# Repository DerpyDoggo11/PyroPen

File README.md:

# Pyropen
A pen with an embedded charlieplexed screen and thermal sensor

## 3D Model Preview

## 3D PCB Preview

## Wiring

## Schematic

## Introduction
Hobby electronics projects can come with a lot of dangers, especially if there is a short between ground and the main voltage line (3.3v) through a component, which is one of the most common faults when hand soldering. These components can get really hot which means placing your finger to sense the temperature is not a super safe option, and is also not very possible for really small components in tight areas. Theres also hundreds of other applications like seeing if a soldering iron is at the good temperature or if something is being heated properly where touching it is not very recommended... 

My solution to this is the PyroPen - a portable thermal sensor that fits in the palm of your hand! It can also replace a regular pen, meaning that you have this sensor on you wherever you go. 

## Bill of Materials 

### 5 Pens:

| Quantity | Components | Price | Link |
|--------- |----------|----------| -----|
| 5  | D1 Mini Pen Refill  (around 67mm long) | $6 | [here](https://www.aliexpress.us/item/3256810502408645.html?spm=a2g0o.productlist.main.1.6d809qLy9qLyLj&algo_pvid=76f2cf68-db1d-471b-9ad9-c0e175543bda&algo_exp_id=76f2cf68-db1d-471b-9ad9-c0e175543bda-0&pdp_ext_f=%7B%22order%22%3A%22431%22%2C%22eval%22%3A%221%22%2C%22fromPage%22%3A%22search%22%7D&pdp_npi=6%40dis%21USD%218.80%216.16%21%21%2158.72%2141.10%21%402101e80b17891628832691912e0dab%2112000053197611078%21sea%21US%217493938711%21X%211%210%21n_tag%3A-29919%3Bd%3Ad260408f%3Bm03_new_user%3A-29895&curPageLogUid=INQ9floTcDND&utparam-url=scene%3Asearch%7Cquery_from%3A%7Cx_object_id%3A1005010688723397%7C_p_origin_prod%3A)
| 1 | Plexiglass sheet | $5 | [here](https://www.aliexpress.us/item/3256807722386926.html?spm=a2g0o.productlist.main.2.39f129e2SERr2S&algo_pvid=185f7068-e484-4aa3-9ff3-0e65a2acbd56&algo_exp_id=185f7068-e484-4aa3-9ff3-0e65a2acbd56-1&pdp_ext_f=%7B%22order%22%3A%22156%22%2C%22eval%22%3A%221%22%2C%22fromPage%22%3A%22search%22%7D&pdp_npi=6%40dis%21USD%218.44%215.23%21%21%2156.35%2134.94%21%402101c4ea17891631287926600e102c%2112000042797704390%21sea%21US%217493938711%21X%211%210%21n_tag%3A-29919%3Bd%3Ad260408f%3Bm03_new_user%3A-29895&curPageLogUid=IFVzF4QWo7zW&utparam-url=scene%3Asearch%7Cquery_from%3A%7Cx_object_id%3A1005007908701678%7C_p_origin_prod%3A)
| 1 | M10 tap and M10 die | $10-25 | [here](https://www.aliexpress.us/item/3256806490105856.html?spm=a2g0o.productlist.main.1.787f45362GMN3x&algo_pvid=6b4764b8-9f9b-4b4b-abaf-7ee7ff8e24d2&algo_exp_id=6b4764b8-9f9b-4b4b-abaf-7ee7ff8e24d2-0&pdp_ext_f=%7B%22order%22%3A%222091%22%2C%22eval%22%3A%221%22%2C%22fromPage%22%3A%22search%22%7D&pdp_npi=6%40dis%21USD%2191.27%2124.16%21%21%2191.27%2124.16%21%402101d9ef17891629153167158e0d3e%2112000037989416687%21sea%21US%217493938711%21X%211%210%21n_tag%3A-29919%3Bd%3Ad260408f%3Bm03_new_user%3A-29895%3BpisId%3A5000000216826354&curPageLogUid=6mPafcKNUYwu&utparam-url=scene%3Asearch%7Cquery_from%3A%7Cx_object_id%3A1005006676420608%7C_p_origin_prod%3A#nav-specification)
| 1 | Black Silicone Sheet | $6 | [here](https://www.aliexpress.us/item/3256803477740534.html?spm=a2g0o.productlist.main.2.18d8BtN8BtN8hz&algo_pvid=ee0522a2-58d0-4bcf-9e30-e4f22c28cf2e&algo_exp_id=ee0522a2-58d0-4bcf-9e30-e4f22c28cf2e-1&pdp_ext_f=%7B%22order%22%3A%22401%22%2C%22eval%22%3A%221%22%2C%22fromPage%22%3A%22search%22%7D&pdp_npi=6%40dis%21USD%216.57%216.57%21%21%216.57%216.57%21%402103081117891632978163784e1014%2112000026705712515%21sea%21US%217493938711%21X%211%210%21n_tag%3A-29919%3Bd%3Ad260408f%3Bm03_new_user%3A-29895&curPageLogUid=KVIebw9Xz1w2&utparam-url=scene%3Asearch%7Cquery_from%3A%7Cx_object_id%3A1005003664055286%7C_p_origin_prod%3A)
| 10 | Contact Springs | $3 | [here](https://www.aliexpress.us/item/3256811981198202.html?spm=a2g0o.productlist.main.22.77f10hiQ0hiQK3&algo_pvid=e18af909-f335-4400-8902-d4f17e02d908&algo_exp_id=e18af909-f335-4400-8902-d4f17e02d908-21&pdp_ext_f=%7B%22order%22%3A%22104%22%2C%22eval%22%3A%221%22%2C%22fromPage%22%3A%22search%22%7D&pdp_npi=6%40dis%21USD%212.11%212.11%21%21%2114.07%2114.07%21%402103094f17891662172853954e0ecd%2112000057659623320%21sea%21US%217493938711%21X%211%210%21n_tag%3A-29919%3Bd%3Ad260408f%3Bm03_new_user%3A-29895&curPageLogUid=K0owjtkuBRbz&utparam-url=scene%3Asearch%7Cquery_from%3A%7Cx_object_id%3A1005012167512954%7C_p_origin_prod%3A) 
| 5 | 5mm Piezoelectric Buzzers | $1 | [here](https://www.lcsc.com/product-detail/C76871.html?s_z=n_q_l_piezoelectric%2520ceramic%2520diaphragm&spm=wm.fly.bg.0.xh___wm.ssy.ml.0-0.ent&lcsc_vid=RwNdUQVeTwANA11XFlZZX1IHRwBZVVwDRlkNV1BWQQMxVlNeTlBYVFxWRldYUTsOAxUeFF5JWBYZEEoKFBINSQcJGk4%3D) 
| 5 | MLX Infrared Sensors | $44 | [here](https://www.lcsc.com/product-detail/C3663116.html?s_z=n_q_MLX90614%2520&spm=wm.fly.bg.0.xh&lcsc_vid=RwNdUQVeTwANA11XFlZZX1IHRwBZVVwDRlkNV1BWQQMxVlNeTlBYX1NQTlVfVjsOAxUeFF5JWBYZEEoKFBINSQcJGk4NBhADEA4cHktTRk8GEwkK)
| 5 | AAAA Batteries | $7 | [here](https://www.amazon.com/AmazonBasics-Everyday-Alkaline-Batteries-8-Pack/dp/B00LH3DTYS?crid=3SYUEZ4T84FRV&dib=eyJ2IjoiMSJ9.xJZDnwcXb6EhPXm3mujCAttCgFNsW5aKTzGClFgmbNEjNBc2EIEIb0whSA5f3VcD3A-52y31u_q1Zwa2tIzaYB4oMPsB5-F0LAKjcA06an0JA-MCbnHJLxW74Hy52UELYeB8vnAcLA--8-hO090HfCUW1_Jm4RTs1KzpswVWjnrPVgvfUBrpNFrdIDRPyOvtuVmp1lYjwbZ0h8qXp7lpeklCB14scTmb_KNGeEhvzpb2sc9qDL89ZA_GC0lTx49BjnFbOIMi3paBV0zKl9BSVV2KHnai9rwA-lfpRBzrJMg.HBTIVsixOTtFYGvLlxr646ElXtiAA0v_4nQW3vVoWGo&dib_tag=se&keywords=aaaa%2Bbatteries%2B10%2Bpack&qid=1789191829&rdc=1&sprefix=aaaa%2Bbatteries%2B10%2Bpac%2Caps%2C321&sr=8-9&th=1)
| 5 | Warm Leds | $1 | [here](https://www.lcsc.com/product-detail/C5440675.html?s_z=n_q_t_warm%2520white%2520led&spm=wm.fly.bg.10.stp___wm.ssy.tc.1.tz&lcsc_vid=RgRbBFdUEQJXXwUER1JXVV1QRQIPUgdUQgRYVAFRR1gxVlNeTlNdUVRWR1NcUzsOAxUeFF5JWBYZEEoKFBINSQcJGk4%3D) 
| 5 | PCBA for PyroPen | $60 | Uploaded PCB fabrication files to JLCPCB and assemble it.   
 
Total cost: **$157**

Cost per pen: **$31.4**

----

## Tools / Other parts:
- M10 Tap and Die (from BOM)
- Hot glue + hot glue gun (or super glue)
- Dremel
- Raspbbery Pi, or any other device that can be used to flash firmware to the ATTINY chip.
- 3D printer

## Assembly
1. 3D print the case and assembly 
2. Use the M10 Tap and Die to thread the three pieces at their corresponding places
3. Cut plexiglass and glue onto the screen case
4. Remove the tabs from the PCB with a dremel (required for meeting the PCBA size requirements)
5. Flash firmware to the PCB with a raspbbery pi (or other method)
6. Solder on the buzzer, MLX sensor, and contact springs to the PCB
7. Insert the assembly into the case.
8. Glue the PCB to the inside of the case with the screen facing out and the button in place
9. Insert the pen refill tightly into the case
10. Mount the remaining components into the case, insert battery, and seal

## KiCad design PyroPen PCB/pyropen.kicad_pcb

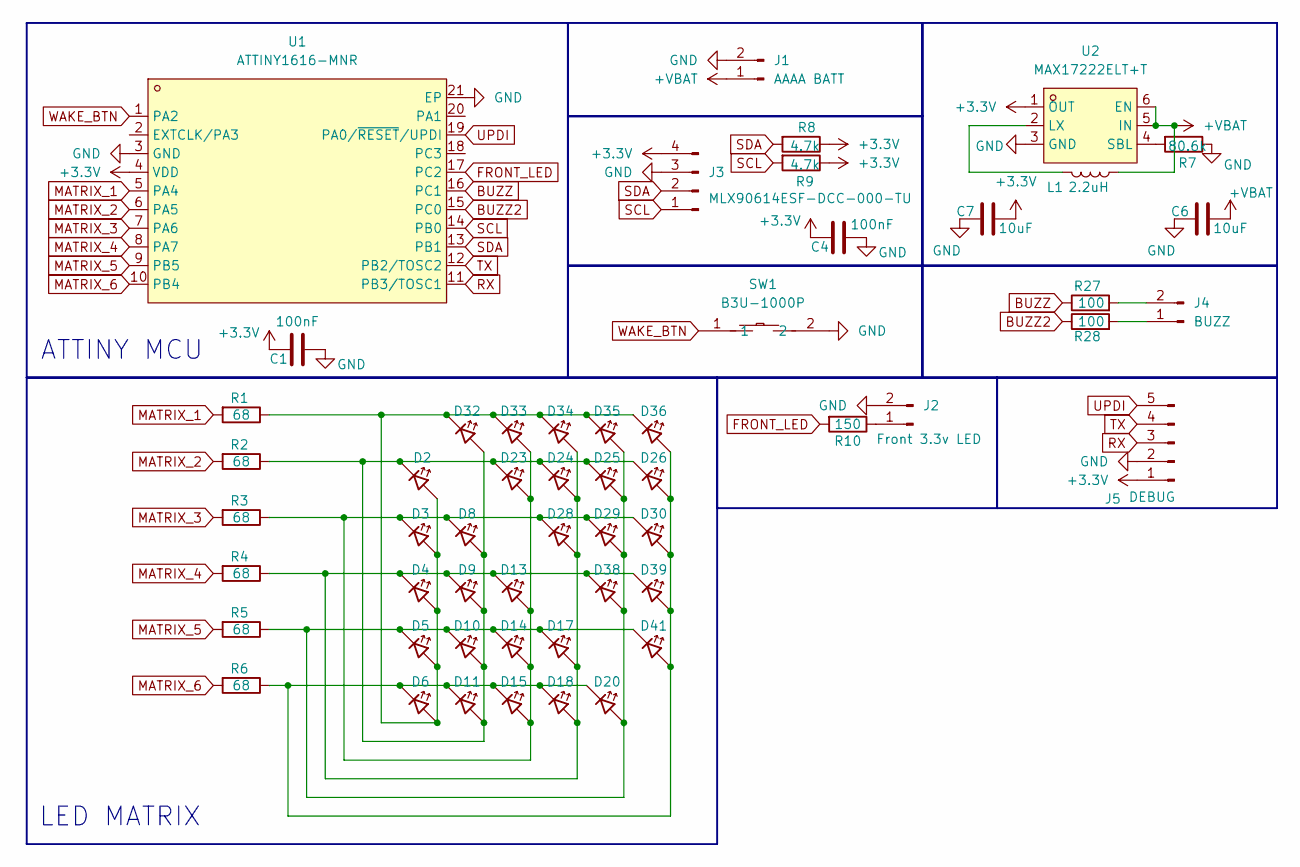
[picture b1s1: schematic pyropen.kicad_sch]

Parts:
C1, C4: 100nF; C_0402_1005Metric
C6, C7: 10uF; C_0603_1608Metric
D2, D3, D4, D5, D6, D8, D9, D10, D11, D13, D14, D15, D17, D18, D20, D23, D24, D25, D26, D28, D29, D30, D32, D33, D34, D35, D36, D38, D39, D41: LED_45deg; LED_0402_1005Metric
J1: AAAA BATT; PinHeader_1x02_P1.00mm_Vertical
J2: Front 3.3v LED; PinHeader_1x02_P1.00mm_Vertical
J3: MLX90614ESF-DCC-000-TU; PinHeader_1x04_P1.00mm_Vertical
J4: BUZZ; PinHeader_1x02_P1.00mm_Vertical
J5: DEBUG; PinHeader_1x05_P1.00mm_Vertical
L1: 2.2uH; L_0603_1608Metric
R1, R2, R3, R4, R5, R6: 68; R_0402_1005Metric
R7: 80.6k; R_0402_1005Metric
R8, R9: 4.7k; R_0402_1005Metric
R10: 150; R_0402_1005Metric
R27, R28: 100; R_0402_1005Metric
SW1: B3U-1000P; KEY-SMD_B3U-1000PM; MPN B3U-1000P; LCSC Part C231329
U1: ATTINY1616-MNR; QFN-20_L3.0-W3.0-P0.40-BL-EP1.7; MPN ATTINY1616-MNR; LCSC Part C507118
U2: MAX17222ELT+T; TDFN-6_L2.0-W2.0-P0.65-BL; MPN MAX17222ELT+T; LCSC Part C1121854

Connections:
+3.3V: C1.1, C4.1, C7.2, J3.4, J5.1, R8.1, R9.1, U1.4 (VDD), U2.1 (OUT)
+VBAT: C6.2, J1.1, L1.1, U2.5 (IN), U2.6 (EN)
BUZZ: R27.1, U1.16 (PC1)
BUZZ2: R28.1, U1.15 (PC0)
FRONT_LED: R10.2, U1.17 (PC2)
GND: C1.2, C4.2, C6.1, C7.1, J1.2, J2.2, J3.3, J5.2, R7.1, SW1.2, U1.3 (GND), U1.21 (EP), U2.3 (GND)
MATRIX_1: R1.2, U1.5 (PA4)
MATRIX_2: R2.2, U1.6 (PA5)
MATRIX_3: R3.2, U1.7 (PA6)
MATRIX_4: R4.2, U1.8 (PA7)
MATRIX_5: R5.2, U1.9 (PB5)
MATRIX_6: R6.2, U1.10 (PB4)
unnamed: D2.2 (A), D3.2 (A), D4.2 (A), D5.2 (A), D6.2 (A), D32.1 (K), D33.1 (K), D34.1 (K), D35.1 (K), D36.1 (K), R1.1
unnamed: D2.1 (K), D8.2 (A), D9.2 (A), D10.2 (A), D11.2 (A), D23.1 (K), D24.1 (K), D25.1 (K), D26.1 (K), D32.2 (A), R2.1
unnamed: D5.1 (K), D10.1 (K), D14.1 (K), D17.1 (K), D20.2 (A), D25.2 (A), D29.2 (A), D35.2 (A), D38.2 (A), D41.1 (K), R5.1
unnamed: D6.1 (K), D11.1 (K), D15.1 (K), D18.1 (K), D20.1 (K), D26.2 (A), D30.2 (A), D36.2 (A), D39.2 (A), D41.2 (A), R6.1
unnamed: D3.1 (K), D8.1 (K), D13.2 (A), D14.2 (A), D15.2 (A), D23.2 (A), D28.1 (K), D29.1 (K), D30.1 (K), D33.2 (A), R3.1
unnamed: D4.1 (K), D9.1 (K), D13.1 (K), D17.2 (A), D18.2 (A), D24.2 (A), D28.2 (A), D34.2 (A), D38.1 (K), D39.1 (K), R4.1
unnamed: J2.1, R10.1
unnamed: J4.1, R28.2
unnamed: J4.2, R27.2
unnamed: L1.2, U2.2 (LX)
unnamed: R7.2, U2.4 (SBL)
RX: J5.3, U1.11 (PB3/TOSC1)
SCL: J3.1, R9.2, U1.14 (PB0)
SDA: J3.2, R8.2, U1.13 (PB1)
TX: J5.4, U1.12 (PB2/TOSC2)
UPDI: J5.5, U1.19 (PA0/~RESET/UPDI)
WAKE_BTN: SW1.1, U1.1 (PA2)

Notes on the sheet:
LED MATRIX
ATTINY MCU

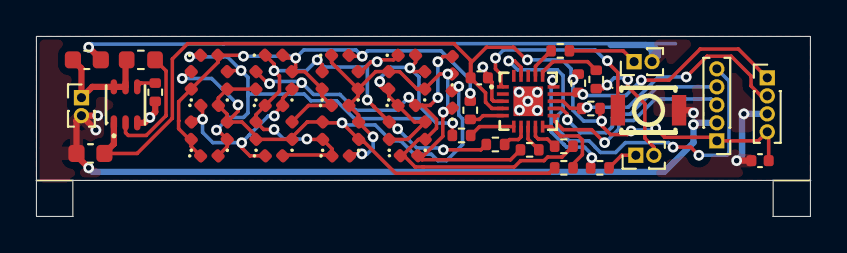
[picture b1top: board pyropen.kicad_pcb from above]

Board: 2 copper layers, 43.0 x 10.0 mm, 55 parts (0 on the bottom side), 29 nets.

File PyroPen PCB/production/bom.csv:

Designator,Footprint,Quantity,Value,LCSC Part #
"C1, C4",0402,2,100nF,
"C6, C7",0603,2,10uF,
"D10, D11, D13, D14, D15, D17, D18, D2, D20, D23, D24, D25, D26, D28, D29, D3, D30, D32, D33, D34, D35, D36, D38, D39, D4, D41, D5, D6, D8, D9",0402,30,LED_45deg,
J1,PinHeader_1x02_P1.00mm_Vertical,1,AAAA BATT,
J2,PinHeader_1x02_P1.00mm_Vertical,1,Front 3.3v LED,
J3,PinHeader_1x04_P1.00mm_Vertical,1,MLX90614ESF-DCC-000-TU,
J4,PinHeader_1x02_P1.00mm_Vertical,1,BUZZ,
J5,PinHeader_1x05_P1.00mm_Vertical,1,DEBUG,
L1,0603,1,2.2uH,
"R1, R2, R3, R4, R5, R6",0402,6,68,
R10,0402,1,150,
"R27, R28",0402,2,100,
R7,0402,1,80.6k,
"R8, R9",0402,2,4.7k,
SW1,KEY-SMD_B3U-1000PM,1,B3U-1000P,C231329
U1,QFN-20_L3.0-W3.0-P0.40-BL-EP1.7,1,ATTINY1616-MNR,C507118
U2,TDFN-6_L2.0-W2.0-P0.65-BL,1,MAX17222ELT+T,C1121854

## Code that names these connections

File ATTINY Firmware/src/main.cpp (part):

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//  and mutes the buzzer (long press).
//
//  Hardware map (from the KiCad schematic/PCB netlist):
//    Charlieplex rails : PA4 PA5 PA6 PA7 PB5 PB4   (MATRIX_1..6, via R1..R6)
//    IR sensor (I2C)   : SDA=PB1  SCL=PB0          (MLX90614 on J3, addr 0x5A)
//    Buzzer (BTL)      : PC1 (BUZZ) + PC0 (BUZZ2)  (piezo across J4)
//    Front LED         : PC2                        (via R10 -> J2, active high)
//    Button            : PA2  (to GND, active low)
//    Serial debug      : TX=PB2  RX=PB3  @115200
// ============================================================================

#include <Arduino.h>
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// ----------------------------------------------------------------------------
// Pins
// ----------------------------------------------------------------------------
static const uint8_t PIN_FRONT_LED = PIN_PC2;
static const uint8_t PIN_BUTTON    = PIN_PA2;
static const uint8_t PIN_BUZZ_A    = PIN_PC1;   // BUZZ
static const uint8_t PIN_BUZZ_B    = PIN_PC0;   // BUZZ2 (driven anti-phase)

// ----------------------------------------------------------------------------
// Charlieplex display: 6 rails, 30 LEDs (fully populated).
// The panel is an irregular dot cloud, so LEDs are ordered here by their
// physical X position: index 0 = leftmost dot ... 29 = rightmost. That makes
// a temperature "bar" as simple as lighting indices 0..n-1.
// LED_AC[i] = {anode rail, cathode rail}. Rails: 0=PA4 1=PA5 2=PA6 3=PA7 4=PB5 5=PB4
// ----------------------------------------------------------------------------
#define NUM_RAILS 6
#define NUM_LEDS  30
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};

// Direct-port descriptors for each rail (fast, glitch-free multiplexing).
// PA4..PA7 live on PORTA bits 4..7; PB4/PB5 on PORTB bits 4/5.
struct RailIO { PORT_t* port; uint8_t bm; };
static RailIO rail[NUM_RAILS] = {
  { &PORTA, PIN4_bm }, // rail0 PA4
  { &PORTA, PIN5_bm }, // rail1 PA5
  { &PORTA, PIN6_bm }, // rail2 PA6
  { &PORTA, PIN7_bm }, // rail3 PA7
  { &PORTB, PIN5_bm }, // rail4 PB5
  { &PORTB, PIN4_bm }, // rail5 PB4
};
static const uint8_t PORTA_RAIL_MASK = PIN4_bm | PIN5_bm | PIN6_bm | PIN7_bm;
static const uint8_t PORTB_RAIL_MASK = PIN4_bm | PIN5_bm;
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static uint32_t frame = 0;

static inline void railsAllHiZ() {
  // Set every rail pin back to input (Hi-Z). Leaves PB0..PB3 (I2C/serial) alone.
  PORTA.DIRCLR = PORTA_RAIL_MASK;
  PORTB.DIRCLR = PORTB_RAIL_MASK;
}
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}

// ----------------------------------------------------------------------------
// Buzzer: piezo is wired across PC1/PC0. Driving them anti-phase gives a
// bridge-tied load (roughly double the voltage swing) for a louder beep.
// Blocking, so keep beeps short.
// ----------------------------------------------------------------------------
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
// ----------------------------------------------------------------------------
void setup() {
  pinMode(PIN_FRONT_LED, OUTPUT);
  digitalWrite(PIN_FRONT_LED, LOW);
  pinMode(PIN_BUTTON, INPUT_PULLUP);
  pinMode(PIN_BUZZ_A, OUTPUT);
  pinMode(PIN_BUZZ_B, OUTPUT);
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    // Error: flash the two end LEDs, no bar.
    frame = (uint32_t)1 | ((uint32_t)1 << (NUM_LEDS - 1));
    if ((now / 300) & 1) frame = 0;
    digitalWrite(PIN_FRONT_LED, LOW);
  } else {
    float t = objC;
    int n = (int)((t - TEMP_MIN_C) / (TEMP_MAX_C - TEMP_MIN_C) * NUM_LEDS + 0.5f);
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    setBar((uint8_t)n);

    bool hot = (t >= HOT_C);
    digitalWrite(PIN_FRONT_LED, hot ? HIGH : LOW);
    if (hot && !buzzerMute && (now - lastBeep) >= 1500) {
      lastBeep = now;
      beep(3200, 60);
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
